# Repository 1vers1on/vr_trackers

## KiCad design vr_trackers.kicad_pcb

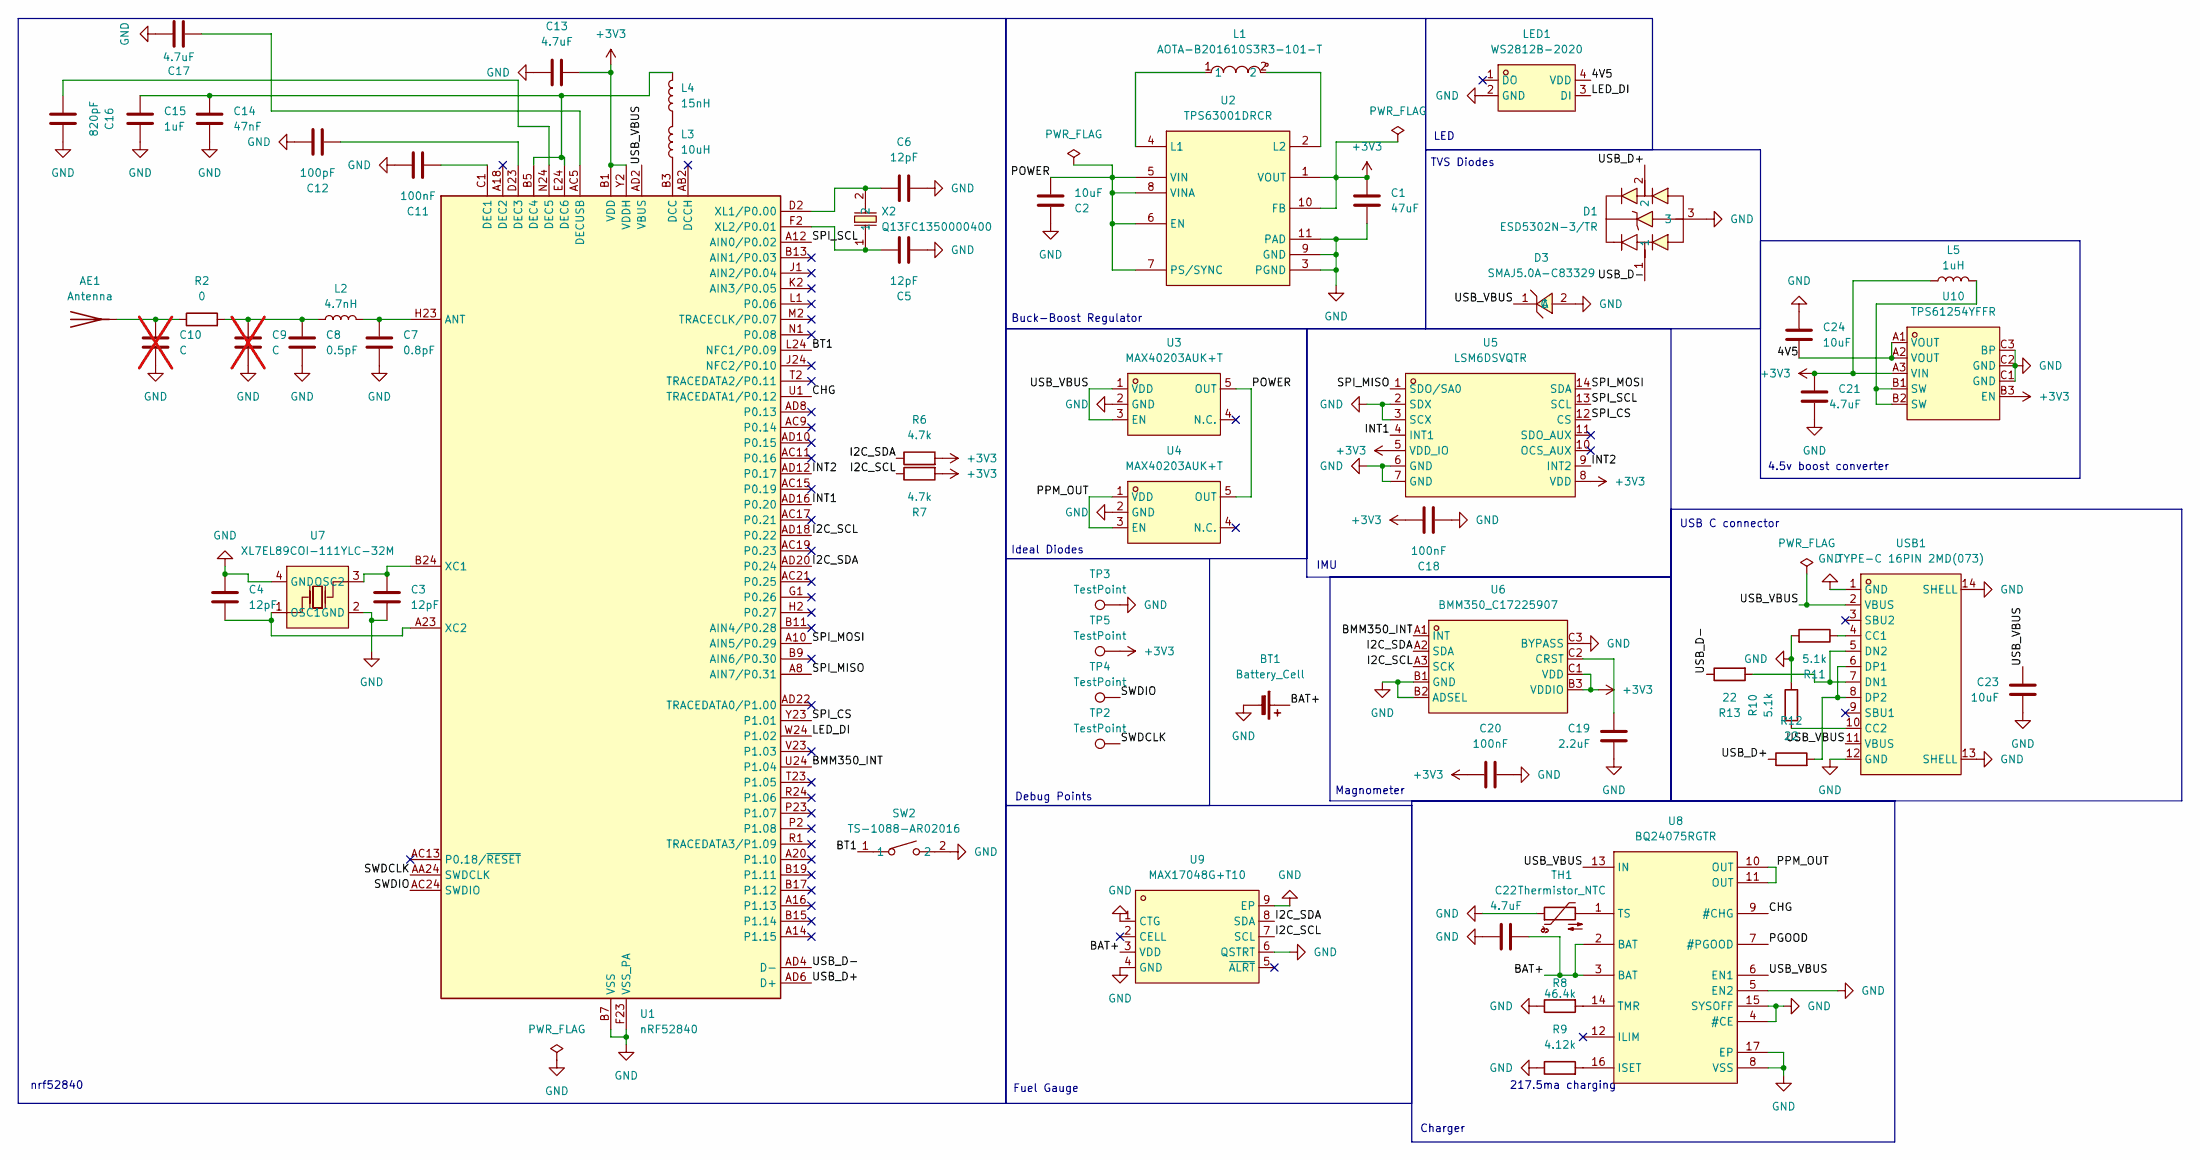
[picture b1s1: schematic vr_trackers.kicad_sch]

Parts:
AE1: Antenna; TI_DN007_2.4GHz
BT1: Battery_Cell; PinHeader_2x01_P2.54mm_Vertical
C1: 47uF; C_0603_1608Metric; LCSC Part C140782
C2, C23: 10uF; C_0402_1005Metric; LCSC Part C315248
C3, C4, C5, C6: 12pF; C_0402_1005Metric; LCSC Part C76948
C7: 0.8pF; C_0402_1005Metric; LCSC Part C327032
C8: 0.5pF; C_0402_1005Metric; LCSC Part C76912
C9, C10: C; C_0402_1005Metric; not fitted
C11, C18, C20: 100nF; C_0402_1005Metric; LCSC Part C60474
C12: 100pF; C_0402_1005Metric; LCSC Part C106200
C13, C17, C22: 4.7uF; C_0402_1005Metric; LCSC Part C23733
C14: 47nF; C_0402_1005Metric; LCSC Part C368599
C15: 1uF; C_0402_1005Metric; LCSC Part C14445
C16: 820pF; C_0402_1005Metric; LCSC Part C161159
C19: 2.2uF; C_0402_1005Metric; LCSC Part C170151
C21: 4.7uF; C_0402_1005Metric
C24: 10uF; C_0402_1005Metric
D1: ESD5302N-3/TR; DFN1006-3L_L1.0-W0.6-P0.35-BL-A; LCSC Part C239822
D3: SMAJ5.0A-C83329; SMA_L4.3-W2.6-LS5.2-RD; LCSC Part C83329
L1: AOTA-B201610S3R3-101-T; IND-SMD_L2.0-W1.6_AOTA-B201610S3R3-101-T; LCSC Part C42411119
L2: 4.7nH; L_0402_1005Metric; LCSC Part C395070
L3: 10uH; L_0603_1608Metric; LCSC Part C76798
L4: 15nH; L_0402_1005Metric; LCSC Part C86059
L5: 1uH; L_0402_1005Metric
LED1: WS2812B-2020; LED-SMD_4P-L2.0-W2.0-TL_WS2812B-2020; LCSC Part C965555
R2: 0; R_0402_1005Metric; LCSC Part C106231
R6, R7: 4.7k; R_0402_1005Metric; LCSC Part C105871
R8: 46.4k; R_0402_1005Metric; LCSC Part C5126026
R9: 4.12k; R_0402_1005Metric; LCSC Part C2480411
R10, R11: 5.1k; R_0402_1005Metric; LCSC Part C105872
R12, R13: 22; R_0402_1005Metric; LCSC Part C114765
SW2: TS-1088-AR02016; SW-SMD_L3.9-W3.0-P4.45; LCSC Part C720477
TH1: Thermistor_NTC; R_0402_1005Metric; LCSC Part C77131
TP2, TP3, TP4, TP5: TestPoint; TestPoint_THTPad_D1.0mm_Drill0.5mm
U1: nRF52840; Nordic_AQFN-73-1EP_7x7mm_P0.5mm; LCSC Part C190794
U2: TPS63001DRCR; VSON-10_L3.0-W3.0-P0.50-TL-EP_TPS62410DRCR; LCSC Part C28060
U3, U4: MAX40203AUK+T; SOT-23-5_L3.0-W1.6-P0.95-LS2.8-BR; LCSC Part C2653639
U5: LSM6DSVQTR; LGA-14_L3.0-W2.5-P0.50-TL; LCSC Part C17496470
U6: BMM350_C17225907; WLCSP-9_L1.3-W1.3-R3-C3-P0.40-TL; LCSC Part C17225907
U7: XL7EL89COI-111YLC-32M; CRYSTAL-SMD_4P-L2.0-W1.6-BL-2; LCSC Part C2965584
U8: BQ24075RGTR; QFN-16_L3.0-W3.0-P0.50-TL-EP1.7; LCSC Part C15464
U9: MAX17048G+T10; TDFN-8_L2.0-W2.0-P0.50-BL-EP1.2; LCSC Part C2682616
U10: TPS61254YFFR; DSBGA-9_L1.3-W1.3-R3-C3-P0.40-BL; LCSC Part C2863435
USB1: TYPE-C 16PIN 2MD(073); USB-C-SMD_TYPE-C-6PIN-2MD-073; LCSC Part C2765186
X2: Q13FC1350000400; FC-135R_L3.2-W1.5; LCSC Part C32346

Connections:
+3V3: C1.1, C13.1, C18.1, C20.2, C21.2, L5.1, R6.2, R7.2, TP5.1, U1.A22 (VDD), U1.AD14 (VDD), U1.AD23 (VDD), U1.B1 (VDD), U1.W1 (VDD), U1.Y2 (VDDH), U2.1 (VOUT), U2.10 (FB), U5.5 (VDD_IO), U5.8 (VDD), U6.B3 (VDDIO), U6.C1 (VDD), U10.A3 (VIN), U10.B3 (EN)
/4V5: C24.2, LED1.4 (VDD), U10.A1 (VOUT), U10.A2 (VOUT)
/BAT+: BT1.1 (+), C22.1, U8.2 (BAT), U8.3 (BAT), U9.3 (VDD)
/BMM350_INT: U1.U24 (P1.04), U6.A1 (INT)
/BT1: SW2.1, U1.L24 (NFC1/P0.09)
/CHG: U1.U1 (TRACEDATA1/P0.12), U8.9 (#CHG)
/I2C_SCL: R7.1, U1.AD18 (P0.22), U6.A3 (SCK), U9.7 (SCL)
/I2C_SDA: R6.1, U1.AD20 (P0.24), U6.A2 (SDA), U9.8 (SDA)
/INT1: U1.AD16 (P0.20), U5.4 (INT1)
/INT2: U1.AD12 (P0.17), U5.9 (INT2)
/LED_DI: LED1.3 (DI), U1.W24 (P1.02)
/PGOOD: U8.7 (#PGOOD)
/POWER: C2.2, U2.5 (VIN), U2.6 (EN), U2.7 (PS/SYNC), U2.8 (VINA), U3.5 (OUT), U4.5 (OUT)
/PPM_OUT: U4.1 (VDD), U4.3 (EN), U8.10 (OUT), U8.11 (OUT)
/SPI_CS: U1.Y23 (P1.01), U5.12 (CS)
/SPI_MISO: U1.A8 (AIN7/P0.31), U5.1 (SDO/SA0)
/SPI_MOSI: U1.A10 (AIN5/P0.29), U5.14 (SDA)
/SPI_SCL: U1.A12 (AIN0/P0.02), U5.13 (SCL)
/SWDCLK: TP2.1, U1.AA24 (SWDCLK)
/SWDIO: TP4.1, U1.AC24 (SWDIO)
/USB_D+: D1.2, R12.1, U1.AD6 (D+)
/USB_D-: D1.1, R13.1, U1.AD4 (D-)
/USB_VBUS: C23.1, D3.1 (C), U1.AD2 (VBUS), U3.1 (VDD), U3.3 (EN), U8.6 (EN1), U8.13 (IN), USB1.2 (VBUS), USB1.11 (VBUS)
GND: AE1.2, BT1.2 (-), C1.2, C2.1, C3.2, C4.1, C5.2, C6.2, C7.1, C8.1, C9.2, C10.2, C11.1, C12.1, C13.2, C14.2, C15.2, C16.1, C17.1, C18.2, C19.1, C20.1, C21.1, C22.2, C23.2, C24.1, D1.3, D3.2 (A), LED1.2 (GND), R8.1, R9.1, R10.1, R11.2, SW2.2, TH1.1, TP3.1, U1.B7 (VSS), U1.EP (VSS), U1.F23 (VSS_PA), U2.3 (PGND), U2.9 (GND), U2.11 (PAD), U3.2 (GND), U4.2 (GND), U5.2 (SDX), U5.3 (SCX), U5.6 (GND), U5.7 (GND), U6.B1 (GND), U6.B2 (ADSEL), U6.C3 (BYPASS), U7.2 (GND), U7.4 (GND), U8.4 (#CE), U8.5 (EN2), U8.8 (VSS), U8.15 (SYSOFF), U8.17 (EP), U9.1 (CTG), U9.4 (GND), U9.6 (QSTRT), U9.9 (EP), U10.C1 (GND), U10.C2 (GND), U10.C3 (BP), USB1.1 (GND), USB1.12 (GND), USB1.13 (SHELL), USB1.14 (SHELL)
unnamed: AE1.1 (A), C10.1, R2.1
unnamed: C8.2, C9.1, L2.1, R2.2
unnamed: L3.2, L4.1
unnamed: L5.2, U10.B1 (SW), U10.B2 (SW)
unnamed: C7.2, L2.2, U1.H23 (ANT)
unnamed: L3.1, U1.B3 (DCC)
unnamed: C11.2, U1.C1 (DEC1)
unnamed: C12.2, U1.D23 (DEC3)
unnamed: C14.1, C15.1, L4.2, U1.B5 (DEC4), U1.E24 (DEC6)
unnamed: C16.2, U1.N24 (DEC5)
unnamed: C17.2, U1.AC5 (DECUSB)
unnamed: C3.1, U1.B24 (XC1), U7.3 (OSC2)
unnamed: C4.2, U1.A23 (XC2), U7.1 (OSC1)
unnamed: C6.1, U1.D2 (XL1/P0.00), X2.2
unnamed: C5.1, U1.F2 (XL2/P0.01), X2.1
unnamed: L1.1, U2.4 (L1)
unnamed: L1.2, U2.2 (L2)
unnamed: C19.2, U6.C2 (CRST)
unnamed: R9.2, U8.16 (ISET)
unnamed: R8.2, U8.14 (TMR)
unnamed: TH1.2, U8.1 (TS)
unnamed: R11.1, USB1.4 (CC1)
unnamed: R10.2, USB1.10 (CC2)
unnamed: R13.2, USB1.5 (DN2), USB1.7 (DN1)
unnamed: R12.2, USB1.6 (DP1), USB1.8 (DP2)

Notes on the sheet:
Fuel Gauge
Magnometer
4.5v boost converter
nrf52840
USB C connector
Charger
LED
Ideal Diodes
TVS Diodes
Buck-Boost Regulator
IMU
217.5ma charging
Debug Points

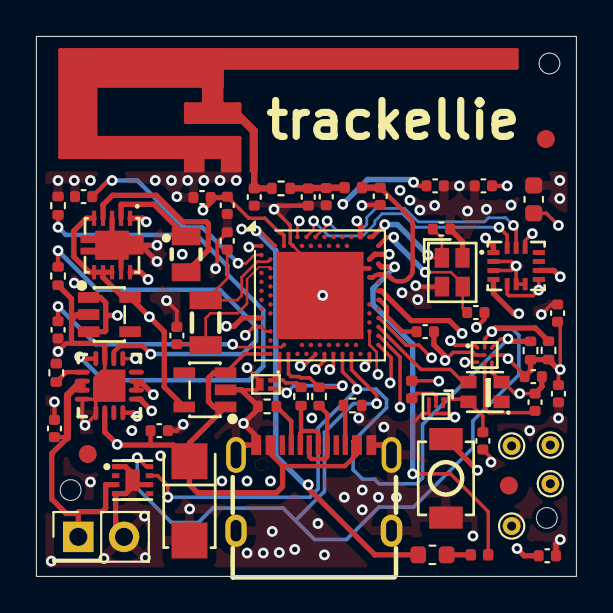
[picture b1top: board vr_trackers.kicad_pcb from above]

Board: 4 copper layers, 30.0 x 30.0 mm, 61 parts (0 on the bottom side), 48 nets.

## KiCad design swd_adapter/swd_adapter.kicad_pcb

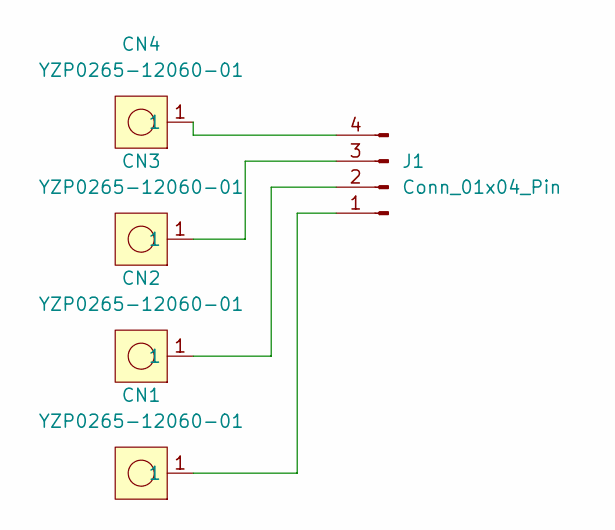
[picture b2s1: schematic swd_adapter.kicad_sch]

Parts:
CN1, CN2, CN3, CN4: YZP0265-12060-01; CONN-TH_YZP0265-12060-01; LCSC Part C5157236
J1: Conn_01x04_Pin; PinHeader_1x04_P2.54mm_Vertical

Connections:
unnamed: CN1.1, J1.1
unnamed: CN2.1, J1.2
unnamed: CN3.1, J1.3
unnamed: CN4.1, J1.4

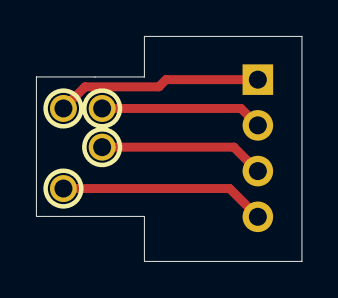
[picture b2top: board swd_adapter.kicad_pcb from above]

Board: 2 copper layers, 14.8 x 12.5 mm, 5 parts (1 on the bottom side), 4 nets.

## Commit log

2026-03-06 First revision of the pcb i think idk when i last commited this
2026-03-06 Second revision of the pcb
2026-03-06 Fix errors
2026-03-06 Move the step file to a models directory
2026-03-06 add west.yml and update gitignore
2026-03-08 Add stuff i forget what
2026-03-12 add firmware stuff and update the pcb
2026-03-12 Update the pcb to add a 4.5v lane, add a lot to the code, and make a second pcb to help programming
2026-03-13 add esb and usb stuff
2026-03-13 add software base code for rust
2026-03-13 give up on rust and do smth to the pcb
2026-03-13 switching to c++ for the software frontend
2026-03-14 stupid stupid stupid stupid usb
